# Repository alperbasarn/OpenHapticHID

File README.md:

# OpenHapticHID
haptic-interactive-human-interface-device

This repository contains the design and manufacturing files of an human interface device as well as the required software to run.

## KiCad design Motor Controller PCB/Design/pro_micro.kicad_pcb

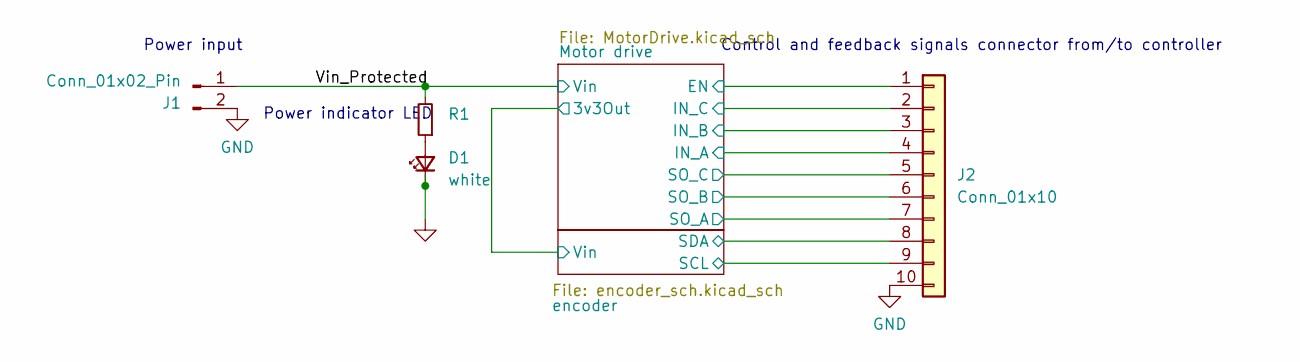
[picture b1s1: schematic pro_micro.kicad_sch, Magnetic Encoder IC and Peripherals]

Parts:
D1: white; LED_0603_1608Metric_Pad1.05x0.95mm_HandSolder
J1: Conn_01x02_Pin; Molex_PicoBlade_53261-0271_1x02-1MP_P1.25mm_Horizontal
J2: Conn_01x10; Molex_PicoBlade_53261-1071_1x10-1MP_P1.25mm_Horizontal
R1: 1k; R_0603_1608Metric_Pad0.98x0.95mm_HandSolder

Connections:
/Motor drive/EN: J2.1; also elsewhere on the board
/Motor drive/IN_A: J2.4; also elsewhere on the board
/Motor drive/IN_B: J2.3; also elsewhere on the board
/Motor drive/IN_C: J2.2; also elsewhere on the board
/Motor drive/SO_A: J2.7; also elsewhere on the board
/Motor drive/SO_B: J2.6; also elsewhere on the board
/Motor drive/SO_C: J2.5; also elsewhere on the board
/encoder/SCL: J2.9; also elsewhere on the board
/encoder/SDA: J2.8; also elsewhere on the board
GND: D1.1 (K), J1.2, J2.10; also elsewhere on the board
unnamed: D1.2 (A), R1.1

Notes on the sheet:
Power indicator LED
Power input
Control and feedback signals connector from/to controller

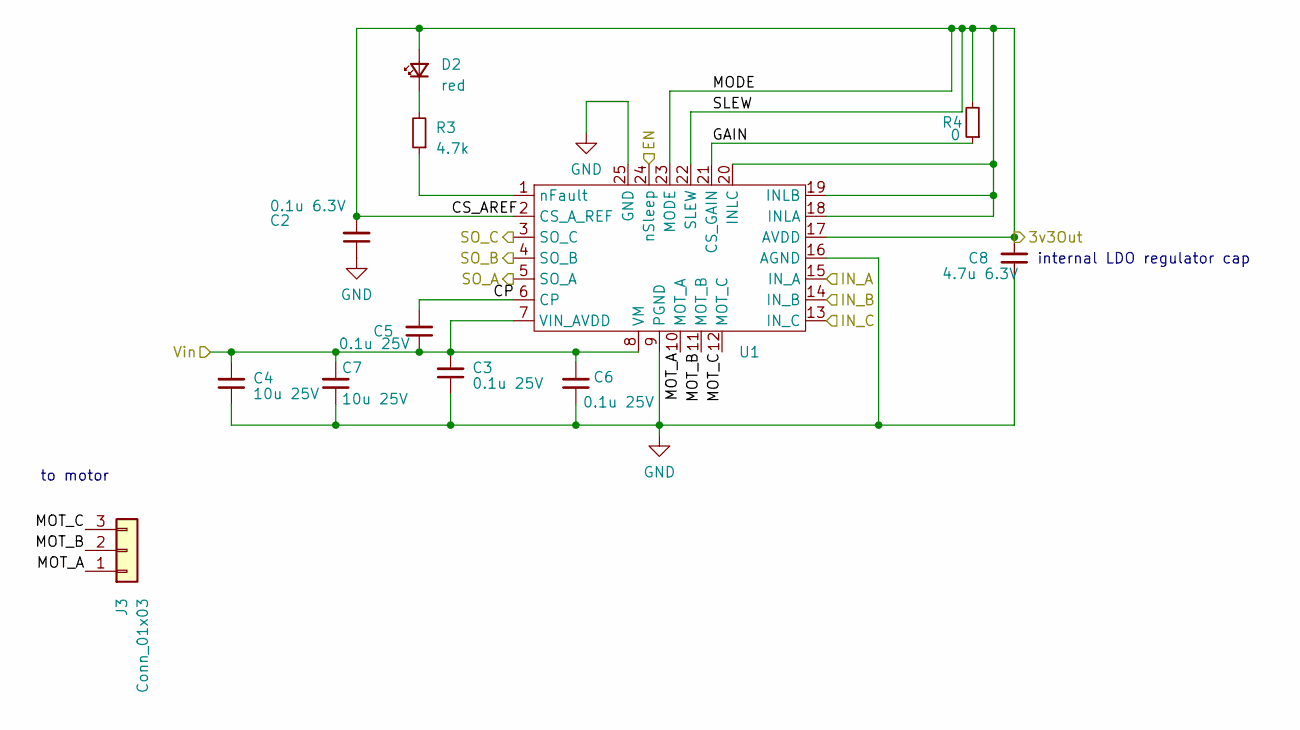
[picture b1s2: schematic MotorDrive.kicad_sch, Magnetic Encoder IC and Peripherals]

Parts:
C2: 0.1u 6.3V; C_0603_1608Metric_Pad1.08x0.95mm_HandSolder
C3, C5, C6: 0.1u 25V; C_0603_1608Metric_Pad1.08x0.95mm_HandSolder
C4: 10u 25V; C_0603_1608Metric_Pad1.08x0.95mm_HandSolder
C7: 10u 25V; CP_EIA-1608-08_AVX-J
C8: 4.7u 6.3V; C_0603_1608Metric_Pad1.08x0.95mm_HandSolder
D2: red; LED_0603_1608Metric_Pad1.05x0.95mm_HandSolder
J3: Conn_01x03; Molex_PicoBlade_53261-0371_1x03-1MP_P1.25mm_Horizontal
R3: 4.7k; R_0603_1608Metric_Pad0.98x0.95mm_HandSolder
R4: 0; R_0603_1608Metric_Pad0.98x0.95mm_HandSolder
U1: IC_DRV8311HRRWR

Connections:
/Motor drive/CP: C5.2, U1.6 (CP)
/Motor drive/CS_AREF: C2.2, C8.2, D2.2 (A), R4.2, U1.2 (CS_A_REF), U1.17 (AVDD), U1.18 (INLA), U1.19 (INLB), U1.20 (INLC), U1.22 (SLEW), U1.23 (MODE); also elsewhere on the board
/Motor drive/EN: U1.24 (nSleep); also elsewhere on the board
/Motor drive/GAIN: R4.1, U1.21 (CS_GAIN)
/Motor drive/IN_A: U1.15 (IN_A); also elsewhere on the board
/Motor drive/IN_B: U1.14 (IN_B); also elsewhere on the board
/Motor drive/IN_C: U1.13 (IN_C); also elsewhere on the board
/Motor drive/MOT_A: J3.1, U1.10 (MOT_A)
/Motor drive/MOT_B: J3.2, U1.11 (MOT_B)
/Motor drive/MOT_C: J3.3, U1.12 (MOT_C)
/Motor drive/SO_A: U1.5 (SO_A); also elsewhere on the board
/Motor drive/SO_B: U1.4 (SO_B); also elsewhere on the board
/Motor drive/SO_C: U1.3 (SO_C); also elsewhere on the board
GND: C2.1, C3.1, C4.1, C6.1, C7.1, C8.1, U1.9 (PGND), U1.16 (AGND), U1.25 (GND); also elsewhere on the board
unnamed: D2.1 (K), R3.2
unnamed 18: R3.1, U1.1 (nFault); also elsewhere on the board

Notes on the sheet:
to motor
internal LDO regulator cap

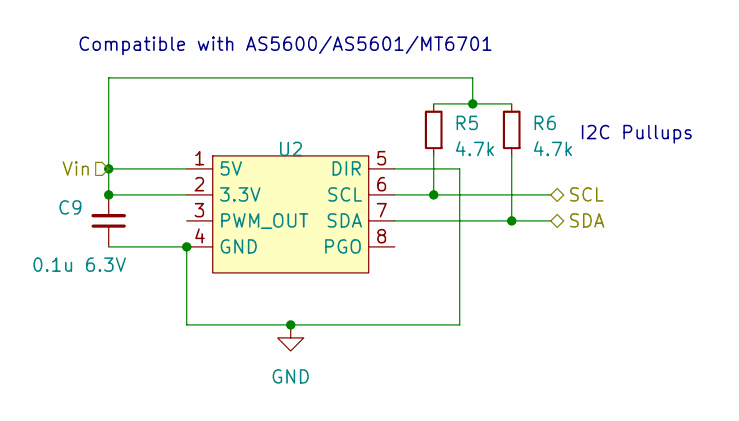
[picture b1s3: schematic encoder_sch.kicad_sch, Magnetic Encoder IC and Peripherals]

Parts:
C9: 0.1u 6.3V; C_0603_1608Metric_Pad1.08x0.95mm_HandSolder
R5, R6: 4.7k; R_0603_1608Metric_Pad0.98x0.95mm_HandSolder
U2: SOIC-8_3.9x4.9mm_P1.27mm

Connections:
/Motor drive/CS_AREF: C9.2, R5.2, R6.2, U2.1 (5V), U2.2 (3.3V); also elsewhere on the board
/encoder/SCL: R5.1, U2.6 (SCL); also elsewhere on the board
/encoder/SDA: R6.1, U2.7 (SDA); also elsewhere on the board
GND: C9.1, U2.4 (GND), U2.5 (DIR); also elsewhere on the board

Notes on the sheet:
Compatible with AS5600/AS5601/MT6701
I2C Pullups

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
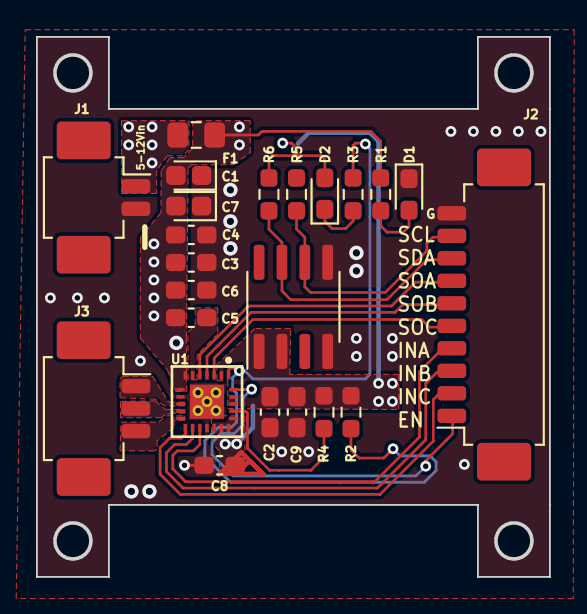
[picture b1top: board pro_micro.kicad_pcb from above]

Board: 2 copper layers, 28.5 x 30.0 mm, 23 parts (0 on the bottom side), 21 nets.

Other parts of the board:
C1: 10u 25V; CP_EIA-1608-08_AVX-J
F1: 2A; Fuse_0805_2012Metric_Pad1.15x1.40mm_HandSolder
R2: 5.1k; R_0603_1608Metric_Pad0.98x0.95mm_HandSolder

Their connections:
/Motor drive/CS_AREF: R2.2; also elsewhere on the board
GND: C1.1; also elsewhere on the board
unnamed 18: R2.1; also elsewhere on the board
